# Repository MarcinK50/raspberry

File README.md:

# RPi Pico W + DHT22 + PMS5003 sensor

```
DHT22 - GPIO16
PMS5003 - TX GPIO8, RX GPIO9

status led:
power status (red) - GPIO10 
wifi status (yellow) - GPIO11
data status (green) - GPIO12
```

## Development branch - differences vs prod branch
- tables have `dev_` prefix
- another development dashboard on Grafana

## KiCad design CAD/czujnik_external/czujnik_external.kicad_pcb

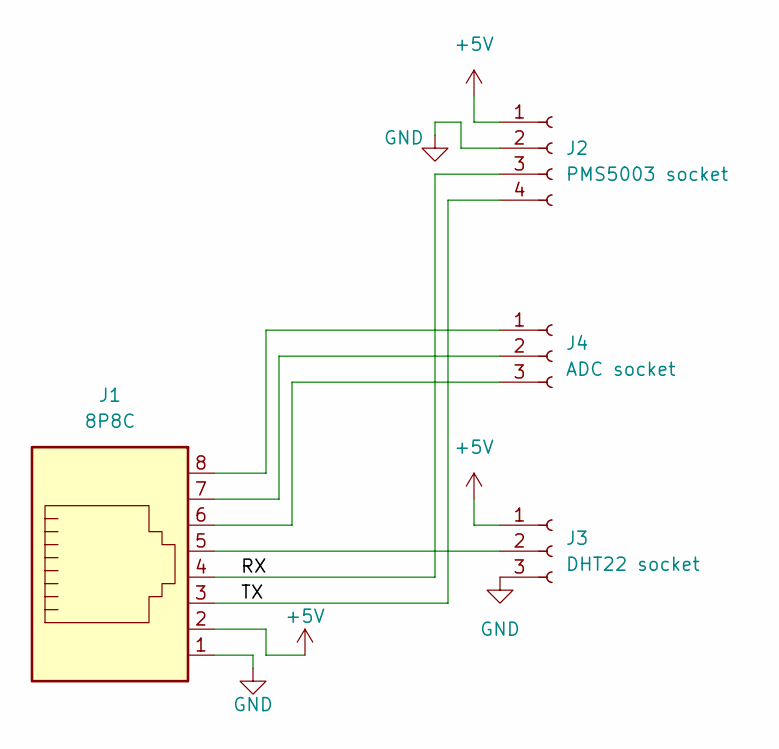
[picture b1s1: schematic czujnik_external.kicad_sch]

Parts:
J1: 8P8C; RJ45_Connfly_DS1128-09-S8xx-S_Horizontal
J2: PMS5003 socket; PinSocket_1x04_P2.54mm_Vertical
J3: DHT22 socket; PinSocket_1x03_P2.54mm_Vertical
J4: ADC socket; PinSocket_1x03_P2.54mm_Vertical

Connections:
+5V: J1.2, J2.1, J3.1
/RX: J1.4, J2.3
/TX: J1.3, J2.4
GND: J1.1, J2.2, J3.3
unnamed: J1.5, J3.2
unnamed: J1.8, J4.1
unnamed: J1.7, J4.2
unnamed: J1.6, J4.3

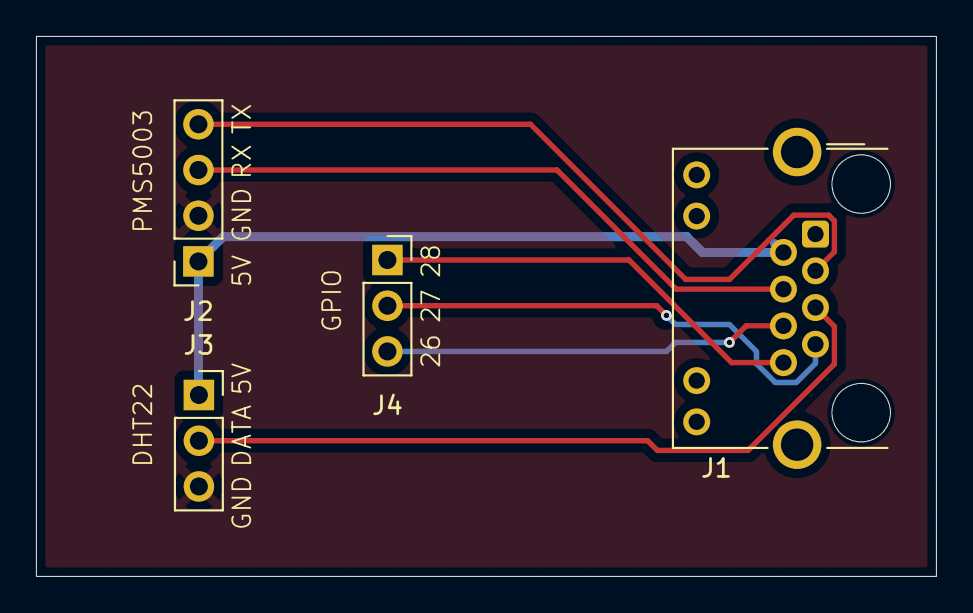
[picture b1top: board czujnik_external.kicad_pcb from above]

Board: 2 copper layers, 50.0 x 30.0 mm, 4 parts (0 on the bottom side), 8 nets.

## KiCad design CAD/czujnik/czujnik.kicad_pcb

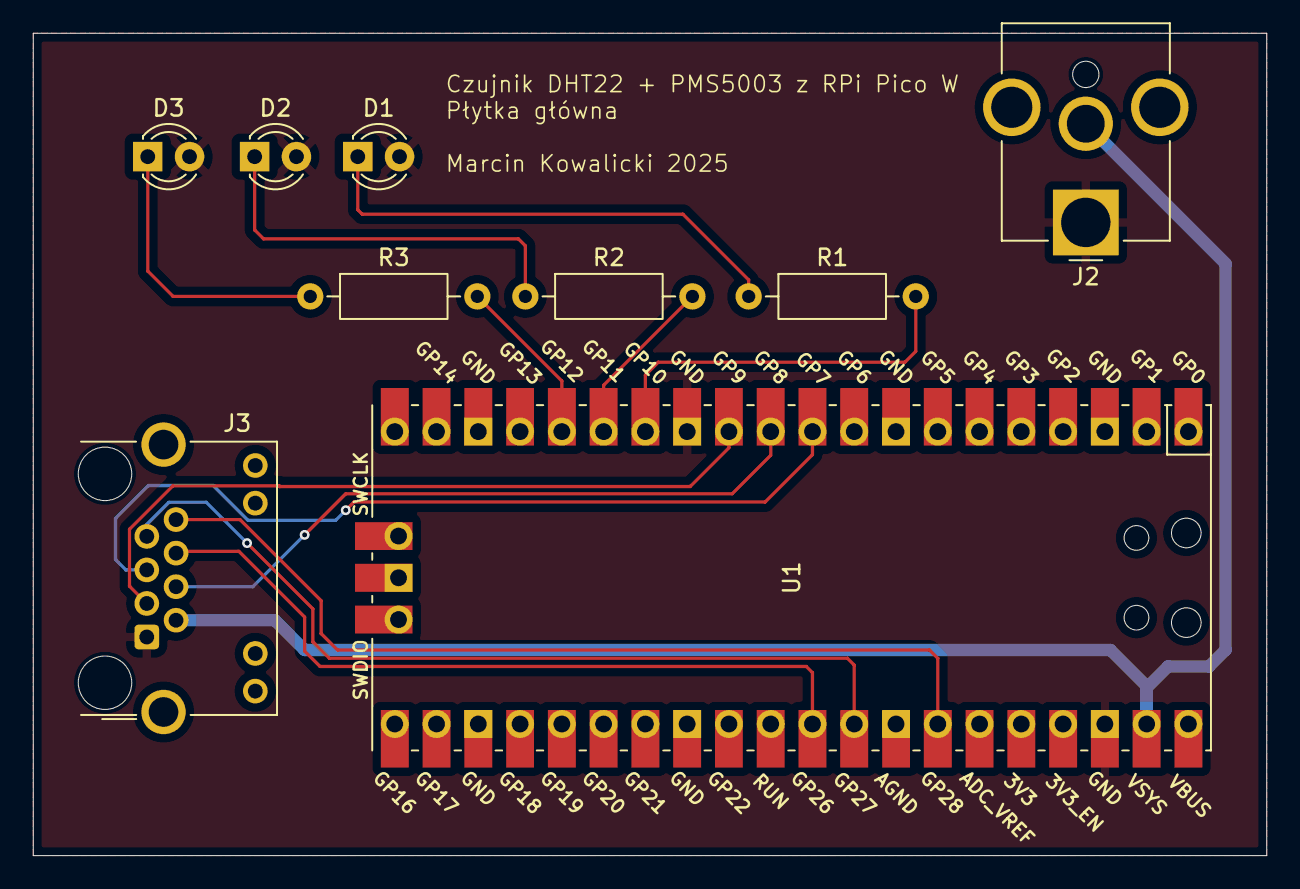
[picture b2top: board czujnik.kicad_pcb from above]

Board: 2 copper layers, 75.0 x 50.0 mm, 9 parts (0 on the bottom side), 14 nets.

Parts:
D1, D2, D3: LED; LED_D3.0mm_Clear
J2: Barrel_Jack; BarrelJack_CUI_PJ-063AH_Horizontal_CircularHoles
J3: 8P8C; RJ45_Connfly_DS1128-09-S8xx-S_Horizontal
R1, R2, R3: 330; R_Axial_DIN0207_L6.3mm_D2.5mm_P10.16mm_Horizontal
U1: Pico; RPi_Pico_SMD_TH

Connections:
+5V: J2.2, J3.2, U1.39 (VSYS)
/DHT22: J3.5, U1.10 (GPIO7)
/RX: J3.4, U1.11 (GPIO8)
/TX: J3.3, U1.12 (GPIO9)
GND: D1.2 (A), D2.2 (A), D3.2 (A), J2.1, J3.1, U1.13 (GND), U1.38 (GND)
unnamed: D1.1 (K), R1.1
unnamed: D2.1 (K), R2.1
unnamed: D3.1 (K), R3.1
unnamed: R1.2, U1.14 (GPIO10)
unnamed: R2.2, U1.15 (GPIO11)
unnamed: R3.2, U1.16 (GPIO12)
unnamed: J3.6, U1.31 (GPIO26_ADC0)
unnamed: J3.7, U1.32 (GPIO27_ADC1)
unnamed: J3.8, U1.34 (GPIO28_ADC2)

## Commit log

2025-03-19 init
2025-03-19 czytanie z czujnika co 2 sekundy
2025-03-19 zapisywanie danych do pliku
2025-03-19 laczenie z wifi i aktualizacja czasu przez NTP
2025-03-19 zera wiodace przy czasie
2025-06-19 refactor i polaczenie przez questdb
2025-06-19 dodanie przykladowego pliku secret i lib mrequests
2025-06-19 dodanie zdjecia
2025-06-19 poprawka importowania biblioteki od UART
2025-06-22 dodanie mozliwosci wylaczenia LED statusu czujnika
2025-06-25 dodanie plikow CAD
2025-11-19 better error handling, add lat and lon fields
2025-12-02 Small corrections, Style update, Comments, More debug info
2025-12-03 move variables to config
2025-12-03 stop sending lat&lon every query
2025-12-03 change location type to int
2025-12-17 add database schema, cleanup git repo
2025-12-17 add logging
2025-12-20 fix getting time from NTP, improve logging
2025-12-21 fix memory issues when sending request by implementing garbage collector
2025-12-21 add log file partitioning
2026-01-07 fix issues with log numbering, implement removing old logs when memory is used
2026-01-07 fix merge from previous commit
2026-01-08 External Sensor Cover
2026-01-13 External Sensor Cover additions
2026-01-13 Added Grafana Extract
2026-01-14 remove zip backups #2
2026-01-14 add production and development branch #5
2026-01-14 add dev branch configuration #5
2026-01-14 change prod setup
2026-01-14 Update README to remove development branch details
2026-01-21 add grafana dashboards #4
2026-01-25 Sensor update
2026-01-25 STLs generation
2026-01-27 STL for device cover
2026-02-09 human readable timestamp
